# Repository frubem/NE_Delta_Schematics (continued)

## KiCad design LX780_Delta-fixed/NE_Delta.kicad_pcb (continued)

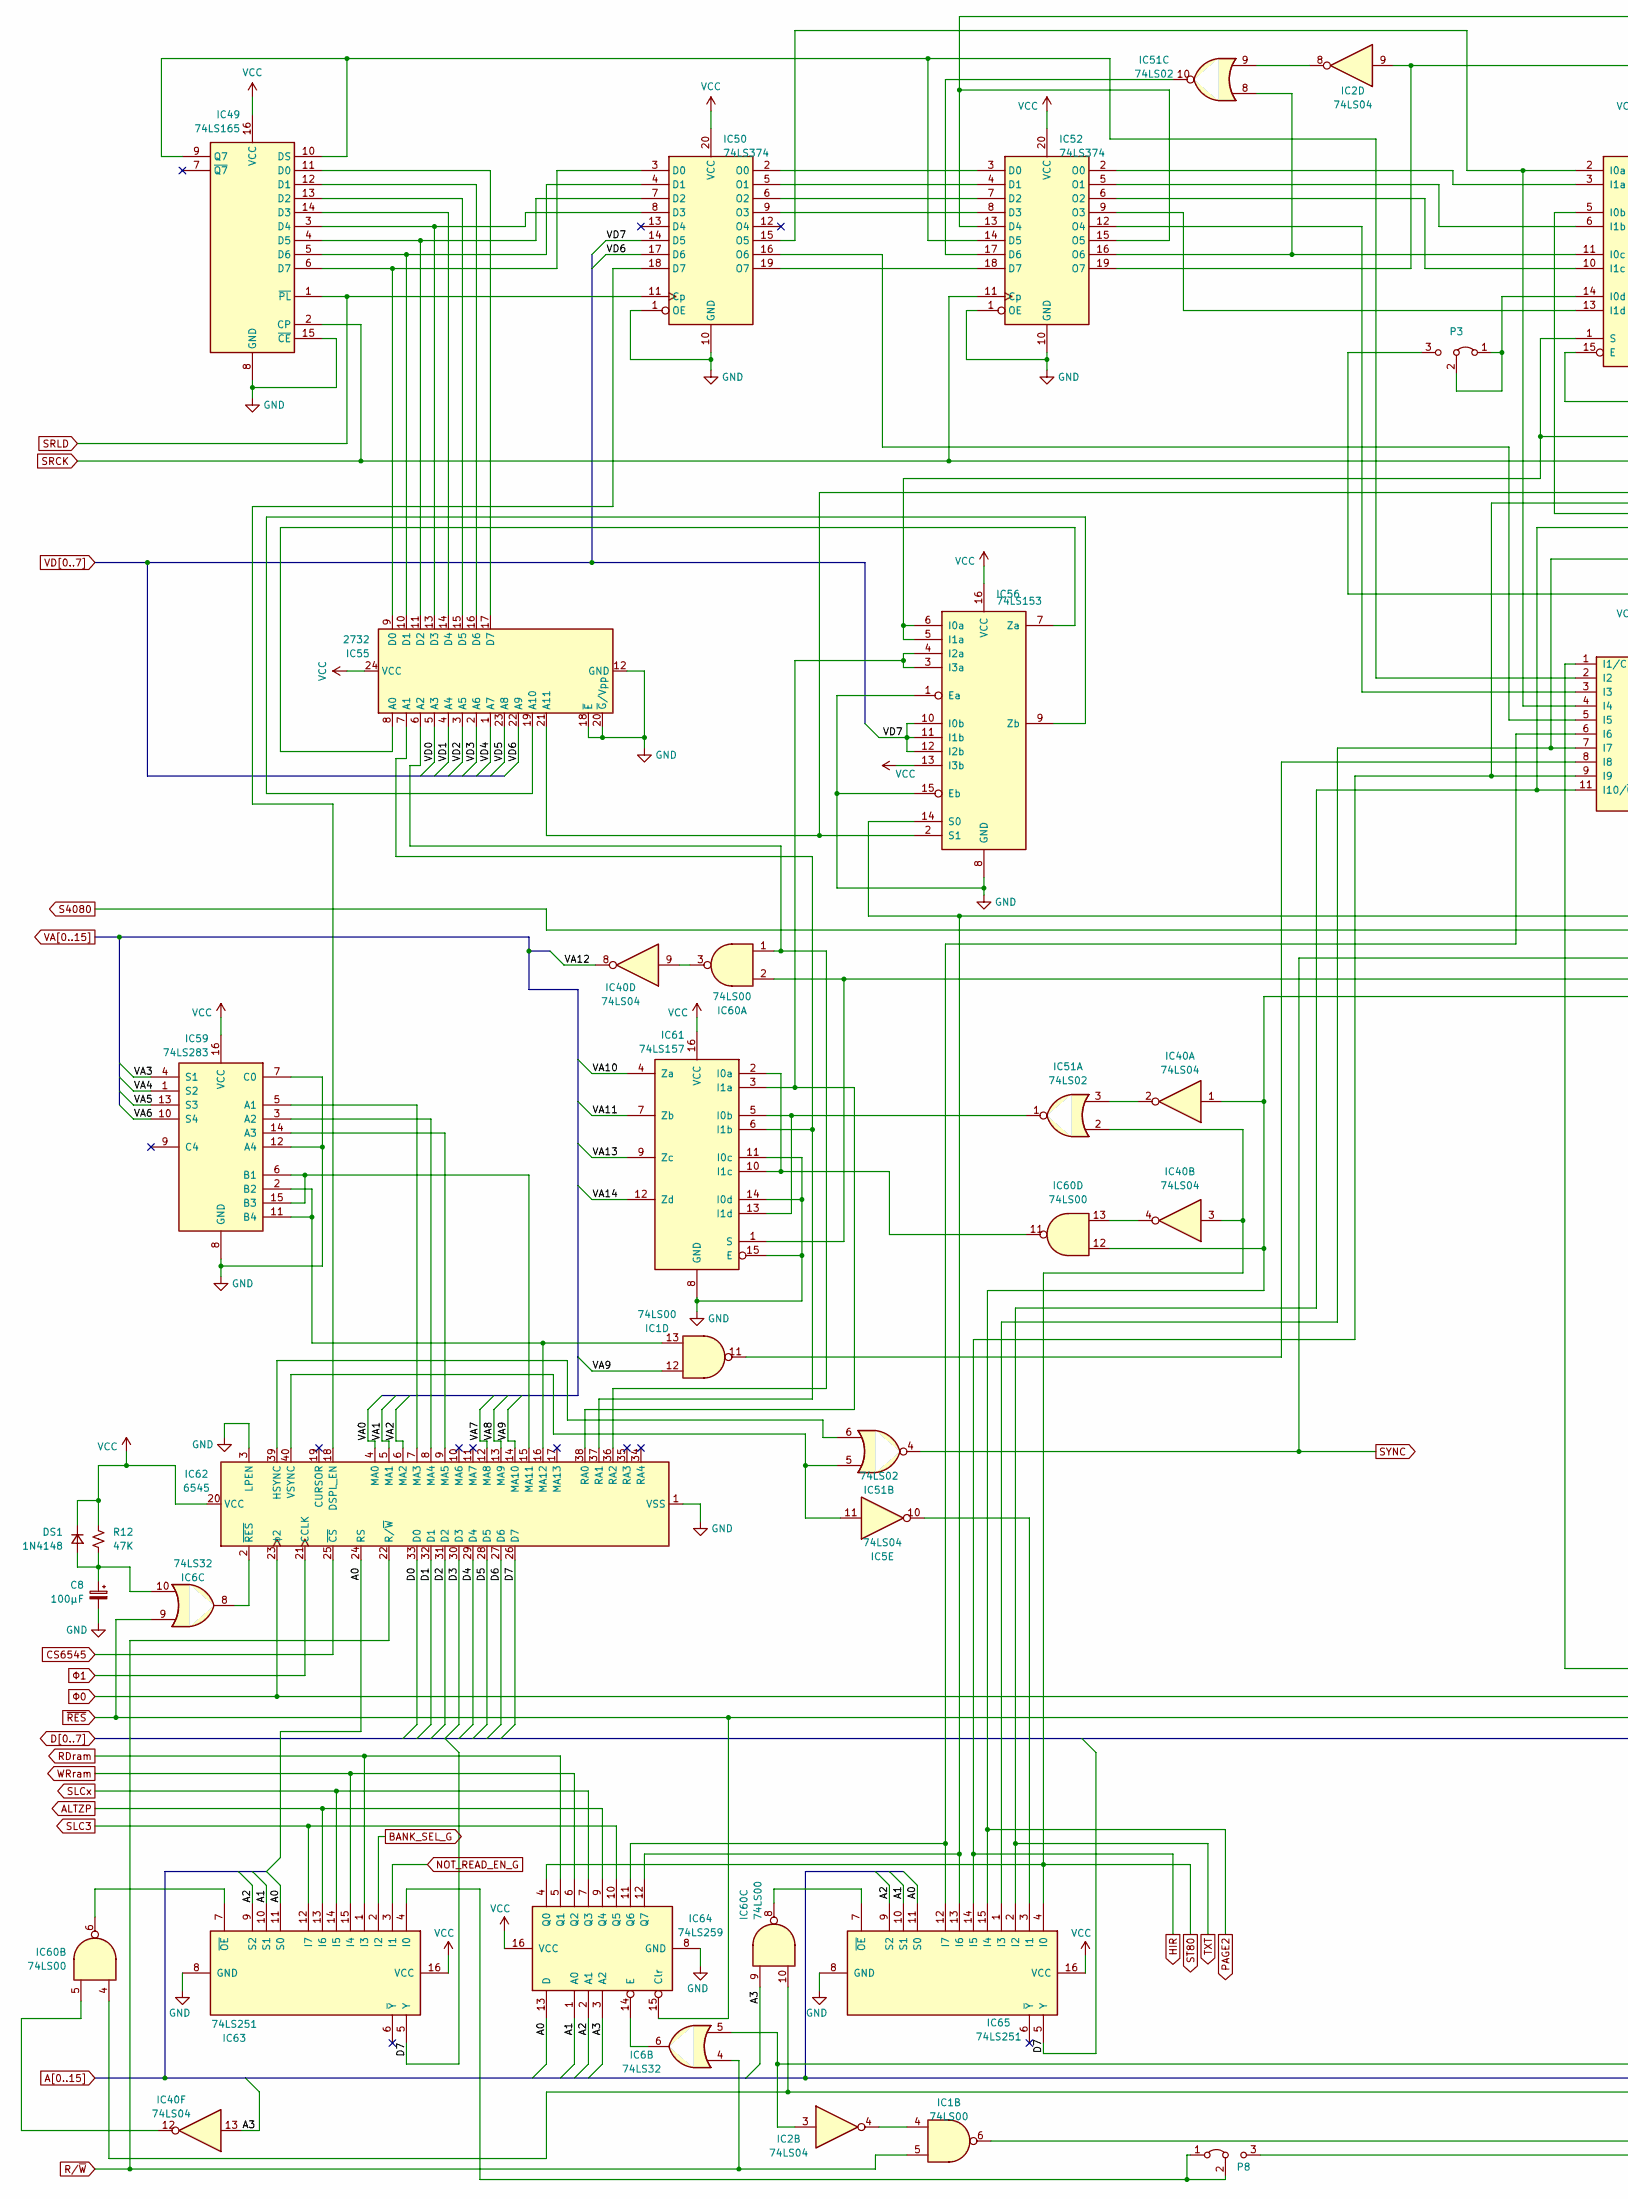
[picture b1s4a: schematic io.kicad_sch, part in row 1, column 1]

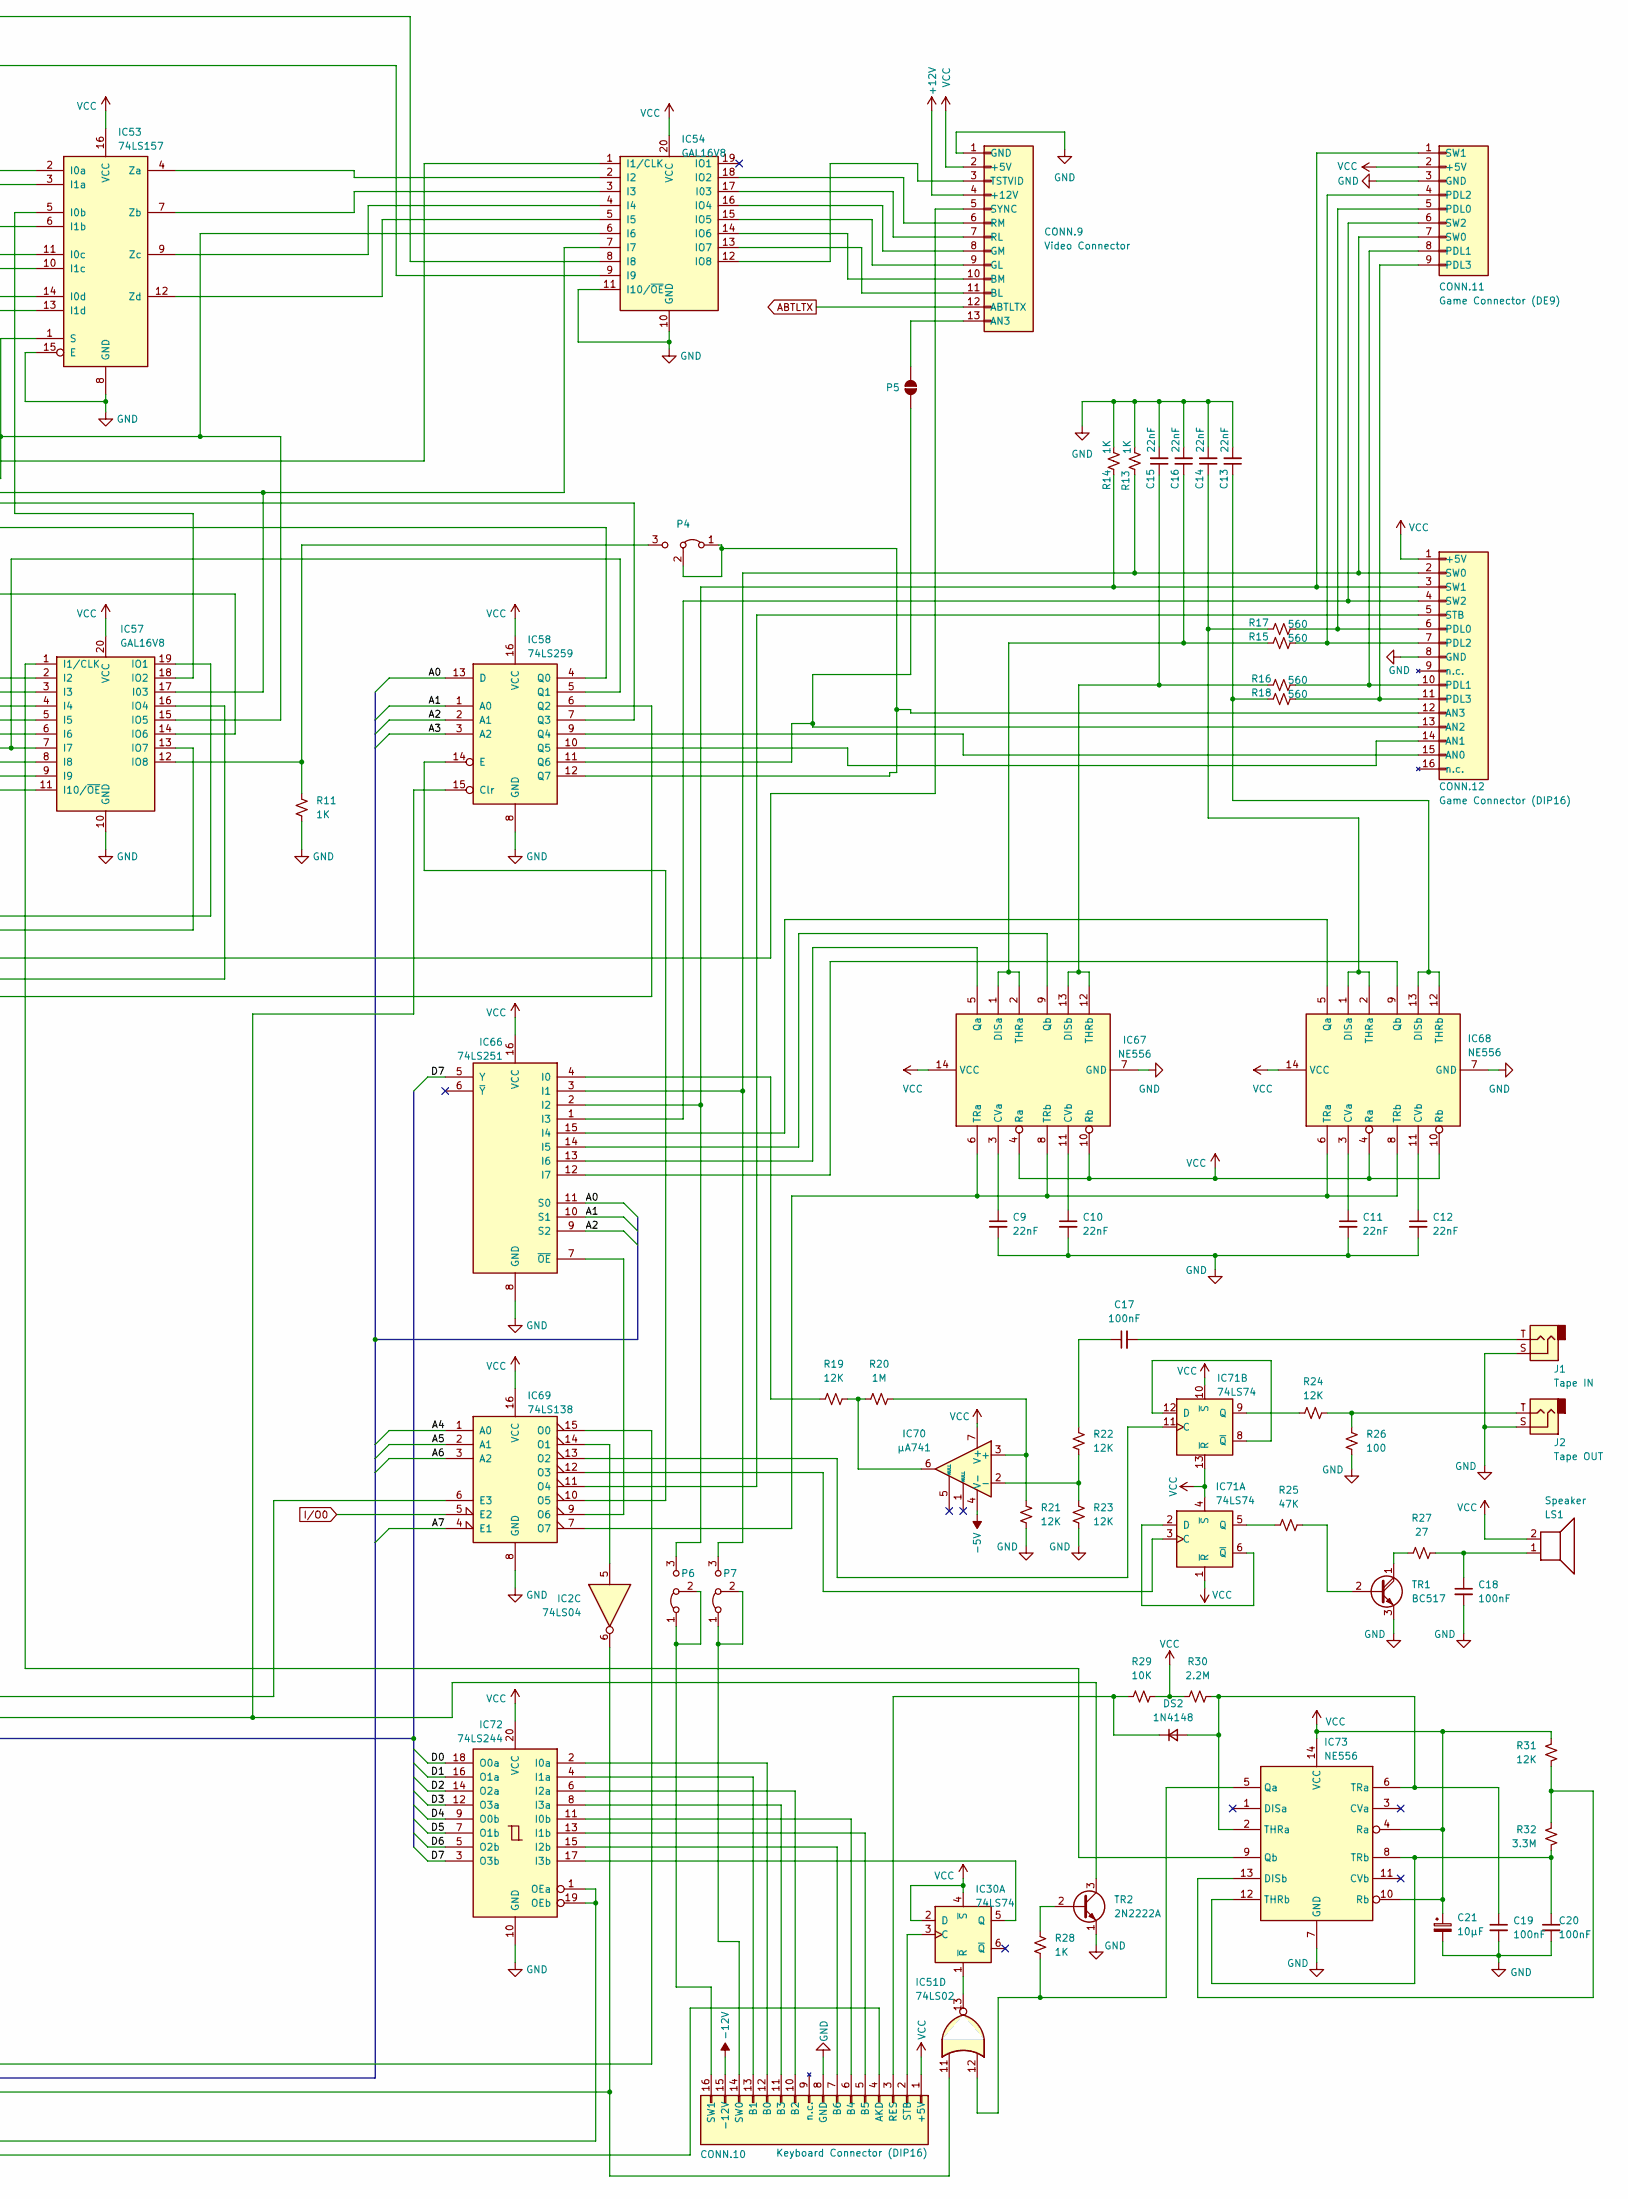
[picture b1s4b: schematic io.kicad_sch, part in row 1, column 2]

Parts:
C8: 100μF; CP_Radial_D8.0mm_P3.50mm
C9, C10, C11, C12, C13, C14, C15, C16: 22nF; C_Disc_D6.0mm_W2.5mm_P5.00mm
C17, C18, C19, C20: 100nF; C_Disc_D6.0mm_W2.5mm_P5.00mm
C21: 10μF; CP_Radial_D8.0mm_P3.50mm
CONN.9: Video Connector; PinSocket_1x13_P2.54mm_Vertical
CONN.10: Keyboard Connector (DIP16); DIP-16_W7.62mm
CONN.11: Game Connector (DE9); DSUB-9_Socket_Horizontal
CONN.12: Game Connector (DIP16); DIP-16_W7.62mm
DS1, DS2: 1N4148; D_DO-35_SOD27_P15.24mm_Horizontal
IC1, IC60: 74LS00; DIP-14_W7.62mm
IC2, IC5, IC40: 74LS04; DIP-14_W7.62mm
IC6: 74LS32; DIP-14_W7.62mm
IC30, IC71: 74LS74; DIP-14_W7.62mm
IC49: 74LS165; DIP-16_W7.62mm
IC50, IC52: 74LS374; DIP-20_W7.62mm
IC51: 74LS02; DIP-14_W7.62mm
IC53, IC61: 74LS157; DIP-16_W7.62mm
IC54, IC57: GAL16V8; DIP-20_W7.62mm
IC55: 2732; DIP-24_W15.24mm
IC56: 74LS153; DIP-16_W7.62mm
IC58, IC64: 74LS259; DIP-16_W7.62mm
IC59: 74LS283; DIP-16_W7.62mm
IC62: 6545; DIP-40_W15.24mm
IC63, IC65, IC66: 74LS251; DIP-16_W7.62mm
IC67, IC68, IC73: NE556; DIP-14_W7.62mm
IC69: 74LS138; DIP-16_W7.62mm
IC70: μA741; DIP-8_W7.62mm
IC72: 74LS244; DIP-20_W7.62mm
J1: Tape IN; Jack_3.5mm_CUI_SJ1-3513N_Horizontal
J2: Tape OUT; Jack_3.5mm_CUI_SJ1-3513N_Horizontal
LS1: Speaker; PinHeader_1x02_P2.54mm_Horizontal
P3, P4, P6, P7, P8: Jumper_3_Bridged12; PinHeader_1x03_P2.54mm_Vertical
P5: SolderJumper_2_Open; SolderJumper-2_P1.3mm_Open_RoundedPad1.0x1.5mm
R11, R13, R14, R28: 1K; R_Axial_DIN0309_L9.0mm_D3.2mm_P15.24mm_Horizontal
R12, R25: 47K; R_Axial_DIN0309_L9.0mm_D3.2mm_P15.24mm_Horizontal
R15, R16, R17, R18: 560; R_Axial_DIN0309_L9.0mm_D3.2mm_P15.24mm_Horizontal
R19, R21, R22, R23, R24, R31: 12K; R_Axial_DIN0309_L9.0mm_D3.2mm_P15.24mm_Horizontal
R20: 1M; R_Axial_DIN0309_L9.0mm_D3.2mm_P15.24mm_Horizontal
R26: 100; R_Axial_DIN0309_L9.0mm_D3.2mm_P15.24mm_Horizontal
R27: 27; R_Axial_DIN0309_L9.0mm_D3.2mm_P15.24mm_Horizontal
R29: 10K; R_Axial_DIN0309_L9.0mm_D3.2mm_P15.24mm_Horizontal
R30: 2.2M; R_Axial_DIN0309_L9.0mm_D3.2mm_P15.24mm_Horizontal
R32: 3.3M; R_Axial_DIN0309_L9.0mm_D3.2mm_P15.24mm_Horizontal
TR1: BC517; TO-92_HandSolder
TR2: 2N2222A; TO-92_HandSolder

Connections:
+5V: C21.1, CONN.9.2 (+5V), CONN.10.1 (+5V), CONN.11.2 (+5V), CONN.12.1 (+5V), DS1.1 (K), IC30.2 (D), IC30.4 (~S), IC49.16 (VCC), IC50.20 (VCC), IC52.20 (VCC), IC53.16 (VCC), IC54.20 (VCC), IC55.24 (VCC), IC56.13 (I3b), IC56.16 (VCC), IC57.20 (VCC), IC58.16 (VCC), IC59.16 (VCC), IC61.16 (VCC), IC62.20 (VCC), IC63.16 (VCC), IC64.16 (VCC), IC65.16 (VCC), IC66.16 (VCC), IC67.4 (Ra), IC67.10 (Rb), IC67.14 (VCC), IC68.4 (Ra), IC68.10 (Rb), IC68.14 (VCC), IC69.16 (VCC), IC70.7 (V+), IC71.1 (~R), IC71.4 (~S), IC71.10 (~S), IC71.13 (~R), IC72.20 (VCC), IC73.4 (Ra), IC73.10 (Rb), IC73.14 (VCC), LS1.2, R12.1, R29.2, R30.1, R31.1; also elsewhere on the board
+12V: CONN.9.4 (+12V); also elsewhere on the board
-5V: IC70.4 (V-); also elsewhere on the board
-12V: CONN.10.15 (-12V); also elsewhere on the board
A0: IC58.13 (D), IC62.24 (RS), IC63.11 (S0), IC64.13 (D), IC65.11 (S0), IC66.11 (S0); also elsewhere on the board
A1: IC58.1 (A0), IC63.10 (S1), IC64.1 (A0), IC65.10 (S1), IC66.10 (S1); also elsewhere on the board
A2: IC58.2 (A1), IC63.9 (S2), IC64.2 (A1), IC65.9 (S2), IC66.9 (S2); also elsewhere on the board
A3: IC40.13, IC58.3 (A2), IC60.9, IC64.3 (A2); also elsewhere on the board
A4: IC69.1 (A0); also elsewhere on the board
A5: IC69.2 (A1); also elsewhere on the board
A6: IC69.3 (A2); also elsewhere on the board
A7: IC69.4 (E1); also elsewhere on the board
ABTLTX: CONN.9.12 (ABTLTX); also elsewhere on the board
ALTZP: IC63.13 (I6), IC64.9 (Q4); also elsewhere on the board
CS6545: IC62.25 (~CS); also elsewhere on the board
D0: IC62.33 (D0), IC72.18 (O0a); also elsewhere on the board
D1: IC62.32 (D1), IC72.16 (O1a); also elsewhere on the board
D2: IC62.31 (D2), IC72.14 (O2a); also elsewhere on the board
D3: IC62.30 (D3), IC72.12 (O3a); also elsewhere on the board
D4: IC62.29 (D4), IC72.9 (O0b); also elsewhere on the board
D5: IC62.28 (D5), IC72.7 (O1b); also elsewhere on the board
D6: IC62.27 (D6), IC72.5 (O2b); also elsewhere on the board
D7: IC62.26 (D7), IC63.5 (Y), IC65.5 (Y), IC66.5 (Y), IC72.3 (O3b); also elsewhere on the board
GND: C8.2, C9.2, C10.2, C11.2, C12.2, C13.2, C14.2, C15.2, C16.2, C18.2, C19.2, C20.2, C21.2, CONN.9.1 (GND), CONN.10.8 (GND), CONN.11.3 (GND), CONN.12.8 (GND), IC49.8 (GND), IC49.15 (~CE), IC50.1 (OE), IC50.10 (GND), IC52.1 (OE), IC52.10 (GND), IC53.8 (GND), IC53.15 (E), IC54.10 (GND), IC54.11 (I10/~OE), IC55.12 (GND), IC55.18 (~E), IC55.20 (~G/Vpp), IC56.1 (Ea), IC56.8 (GND), IC56.15 (Eb), IC57.10 (GND), IC58.8 (GND), IC59.7 (C0), IC59.8 (GND), IC59.12 (A4), IC61.8 (GND), IC61.11 (I0c), IC61.14 (I0d), IC61.15 (E), IC62.1 (VSS), IC62.3 (LPEN), IC63.8 (GND), IC64.8 (GND), IC65.8 (GND), IC66.8 (GND), IC67.7 (GND), IC68.7 (GND), IC69.8 (GND), IC72.10 (GND), IC73.7 (GND), J1.S, J2.S, R11.2, R13.2, R14.2, R21.2, R23.2, R26.2, TR1.3 (E), TR2.1 (E); also elsewhere on the board
HIR: IC57.9 (I9), IC58.7 (Q3), IC65.14 (I5); also elsewhere on the board
I/O0: IC69.5 (E2); also elsewhere on the board
unnamed: C17.1, R22.1
unnamed: C17.2, J1.T
unnamed: C18.1, LS1.1, R27.2
unnamed: CONN.9.11 (BL), IC54.13 (IO7)
unnamed: CONN.9.10 (BM), IC54.14 (IO6)
unnamed: CONN.9.9 (GL), IC54.15 (IO5)
unnamed: CONN.9.8 (GM), IC54.16 (IO4)
unnamed: CONN.9.7 (RL), IC54.17 (I03)
unnamed: CONN.9.6 (RM), IC54.18 (IO2)
unnamed: CONN.9.3 (TSTVID), IC54.12 (IO8)
unnamed: CONN.10.4 (AKD), P8.3 (B)
unnamed: CONN.10.12 (B0), IC72.2 (I0a)
unnamed: CONN.10.13 (B1), IC72.4 (I1a)
unnamed: CONN.10.10 (B2), IC72.6 (I2a)
unnamed: CONN.10.11 (B3), IC72.8 (I3a)
unnamed: CONN.10.6 (B4), IC72.11 (I0b)
unnamed: CONN.10.5 (B5), IC72.13 (I1b)
unnamed: CONN.10.7 (B6), IC72.15 (I2b)
unnamed: CONN.10.3 (RES), DS2.1 (K), R29.1
unnamed: CONN.10.2 (STB), IC30.3 (C)
unnamed: CONN.10.14 (SW0), P7.1 (A), P7.2 (C)
unnamed: CONN.10.16 (SW1), P6.1 (A), P6.2 (C)
unnamed: CONN.11.5 (PDL0), CONN.12.6 (PDL0), R17.2
unnamed: CONN.11.8 (PDL1), CONN.12.10 (PDL1), R16.2
unnamed: CONN.11.4 (PDL2), CONN.12.7 (PDL2), R15.2
unnamed: CONN.11.9 (PDL3), CONN.12.11 (PDL3), R18.2
unnamed: CONN.11.7 (SW0), CONN.12.2 (SW0), IC66.3 (I1), P7.3 (B), R13.1
unnamed: CONN.11.1 (SW1), CONN.12.3 (SW1), IC66.2 (I2), P6.3 (B), R14.1
unnamed: CONN.11.6 (SW2), CONN.12.4 (SW2), IC66.1 (I3)
unnamed: CONN.12.15 (AN0), IC58.9 (Q4)
unnamed: CONN.12.14 (AN1), IC58.10 (Q5)
unnamed: CONN.12.12 (AN3), IC58.12 (Q7), P4.1 (A), P4.2 (C)
unnamed: CONN.12.5 (STB), IC69.11 (O4)
unnamed: C8.1, DS1.2 (A), IC6.10, R12.2
unnamed: C19.1, DS2.2 (A), IC73.2 (THRa), IC73.6 (TRa), R30.2
unnamed: IC1.4, IC2.4
unnamed: IC2.6, IC51.11, IC60.4, IC60.10
unnamed: IC2.8, IC51.9
unnamed: IC30.5 (Q), IC72.17 (I3b)
unnamed: IC30.1 (~R), IC51.13
unnamed: IC40.2, IC51.3
unnamed: IC40.4, IC60.13
unnamed: IC40.9, IC60.3
unnamed: IC40.12, IC60.5
unnamed: IC49.11 (D0), IC55.17 (D7)
unnamed: IC49.12 (D1), IC55.16 (D6)
unnamed: IC49.13 (D2), IC55.15 (D5)
unnamed: IC49.14 (D3), IC55.14 (D4)
unnamed: IC49.3 (D4), IC50.8 (D3), IC55.13 (D3)
unnamed: IC49.4 (D5), IC50.7 (D2), IC55.11 (D2)
unnamed: IC49.5 (D6), IC50.4 (D1), IC55.10 (D1)
unnamed: IC49.6 (D7), IC50.3 (D0), IC55.9 (D0)
unnamed: IC49.9 (Q7), IC49.10 (DS), IC52.14 (D5), IC57.2 (I2)
unnamed: IC50.18 (D7), IC62.18 (DSPL_EN)
unnamed: IC50.2 (O0), IC52.3 (D0)
unnamed: IC50.5 (O1), IC52.4 (D1)
unnamed: IC50.6 (O2), IC52.7 (D2)
unnamed: IC50.9 (O3), IC52.8 (D3)
unnamed: IC50.15 (O5), IC53.2 (I0a), IC57.4 (I4)
unnamed: IC50.16 (O6), IC57.5 (I5)
unnamed: IC50.19 (O7), IC52.18 (D7)
unnamed: IC52.13 (D4), IC52.15 (O5), IC54.8 (I8)
unnamed: IC51.10, IC52.17 (D6)
unnamed: IC52.2 (O0), IC53.3 (I1a)
unnamed: IC52.5 (O1), IC53.6 (I1b)
unnamed: IC52.6 (O2), IC53.10 (I1c)
unnamed: IC52.9 (O3), IC53.13 (I1d)
unnamed: IC52.12 (O4), IC57.3 (I3)
unnamed: IC51.8, IC52.16 (O6), IC53.11 (I0c)
unnamed: IC2.9, IC52.19 (O7), IC54.9 (I9)
unnamed: IC53.5 (I0b), IC57.18 (IO2)
unnamed: IC53.14 (I0d), P3.1 (A), P3.2 (C)
unnamed: IC53.1 (S), IC54.6 (I6), IC56.5 (I1a), IC56.6 (I0a), IC57.15 (IO5)
unnamed: IC53.4 (Za), IC54.2 (I2)
unnamed: IC53.7 (Zb), IC54.3 (I3)
unnamed: IC53.9 (Zc), IC54.4 (I4)
unnamed: IC53.12 (Zd), IC54.5 (I5)
unnamed: IC54.7 (I7), IC55.21 (A11), IC56.2 (S1), IC57.17 (I03)
unnamed: IC55.8 (A0), IC56.7 (Za)
unnamed: IC55.7 (A1), IC61.6 (I1b), IC62.37 (RA1)
unnamed: IC55.6 (A2), IC60.1, IC62.36 (RA2)
unnamed: IC55.19 (A10), IC56.9 (Zb)
unnamed: IC56.3 (I3a), IC56.4 (I2a), IC61.3 (I1a), IC62.38 (RA0)
unnamed: IC56.14 (S0), IC57.19 (IO1), IC64.12 (Q7), IC65.13 (I6)
unnamed: IC57.1 (I1/CLK), IC73.9 (Qb)
unnamed: IC57.6 (I6), IC64.11 (Q6), IC65.12 (I7)
unnamed: IC57.7 (I7), IC58.5 (Q1), IC65.1 (I3)
unnamed: IC1.11, IC57.8 (I8)
unnamed: IC57.16 (IO4), IC60.2, IC61.1 (S)
unnamed: IC57.14 (IO6), P3.3 (B)
unnamed: IC57.12 (IO8), P4.3 (B), R11.1
unnamed: IC58.14 (E), IC69.10 (O5)
unnamed: IC59.5 (A1), IC62.7 (MA3)
unnamed: IC59.3 (A2), IC62.8 (MA4)
unnamed: IC59.14 (A3), IC62.9 (MA5)
unnamed: IC59.6 (B1), IC59.15 (B3), IC62.15 (MA11)
unnamed: IC1.13, IC59.2 (B2), IC59.11 (B4), IC62.16 (MA12)
unnamed: IC60.11, IC61.2 (I0a), IC61.10 (I1c)
unnamed: IC51.1, IC61.5 (I0b), IC61.13 (I1d)
unnamed: IC51.6, IC62.39 (HSYNC)
unnamed: IC5.11, IC51.5, IC62.40 (VSYNC)
unnamed: IC6.8, IC62.2 (~RES)
unnamed: IC63.4 (I0), P8.1 (A), P8.2 (C)
unnamed 261: IC63.3 (I1); also elsewhere on the board
unnamed: IC60.6, IC63.7 (~OE)
unnamed: IC6.6, IC64.14 (E)
unnamed: IC5.10, IC65.3 (I1)
unnamed: IC60.8, IC65.7 (~OE)
unnamed: IC66.4 (I0), R19.1
unnamed: IC66.15 (I4), IC68.5 (Qa)
unnamed: IC66.14 (I5), IC67.9 (Qb)
unnamed: IC66.13 (I6), IC67.5 (Qa)
unnamed: IC66.12 (I7), IC68.9 (Qb)
unnamed: IC66.7 (~OE), IC69.9 (O6)
unnamed: C9.1, IC67.3 (CVa)
unnamed: C10.1, IC67.11 (CVb)
unnamed: C16.1, IC67.1 (DISa), IC67.2 (THRa), R15.1
unnamed: C15.1, IC67.12 (THRb), IC67.13 (DISb), R16.1
unnamed: IC67.6 (TRa), IC67.8 (TRb), IC68.6 (TRa), IC68.8 (TRb), IC69.7 (O7)
unnamed: C11.1, IC68.3 (CVa)
unnamed: C12.1, IC68.11 (CVb)
unnamed: C14.1, IC68.1 (DISa), IC68.2 (THRa), R17.1
unnamed: C13.1, IC68.12 (THRb), IC68.13 (DISb), R18.1
unnamed: IC2.3, IC6.5, IC69.15 (O0)
unnamed: IC2.5, IC69.14 (O1)
unnamed: IC69.13 (O2), IC71.11 (C)
unnamed: IC69.12 (O3), IC71.3 (C)
unnamed: IC70.3 (+), R20.2, R21.1
unnamed: IC70.2 (-), R22.2, R23.1
unnamed: IC70.6, R19.2, R20.1
unnamed: IC71.2 (D), IC71.6 (~Q)
unnamed: IC71.5 (Q), R25.1
unnamed: IC71.8 (~Q), IC71.12 (D)
unnamed: IC71.9 (Q), R24.1
unnamed: IC1.6, IC72.1 (OEa), IC72.19 (OEb)
unnamed: IC73.13 (DISb), R31.2, R32.1
unnamed: IC51.12, IC73.5 (Qa), R28.2
unnamed: C20.1, IC73.8 (TRb), IC73.12 (THRb), R32.2
unnamed: J2.T, R24.2, R26.1
unnamed: R25.2, TR1.2 (B)
unnamed: R27.1, TR1.1 (C)
unnamed: R28.1, TR2.2 (B)
PAGE2: IC40.1, IC58.6 (Q2), IC60.12, IC65.15 (I4); also elsewhere on the board
RDram: IC63.1 (I3), IC64.5 (Q1); also elsewhere on the board
R/~W: IC1.5, IC6.4, IC62.22 (R/~W); also elsewhere on the board
S4080: IC57.13 (IO7); also elsewhere on the board
SLC3: IC63.12 (I7), IC64.10 (Q5); also elsewhere on the board
SLCx: IC63.14 (I5), IC64.7 (Q3); also elsewhere on the board
SRCK: IC49.2 (CP), IC52.11 (Cp), IC54.1 (I1/CLK); also elsewhere on the board
SRLD: IC49.1 (~PL), IC50.11 (Cp); also elsewhere on the board
ST80: IC40.3, IC51.2, IC64.4 (Q0), IC65.4 (I0); also elsewhere on the board
SYNC: CONN.9.5 (SYNC), IC51.4; also elsewhere on the board
TXT: IC57.11 (I10/~OE), IC58.4 (Q0), IC65.2 (I2); also elsewhere on the board
VA0: IC62.4 (MA0); also elsewhere on the board
VA1: IC62.5 (MA1); also elsewhere on the board
VA2: IC62.6 (MA2); also elsewhere on the board
VA3: IC59.4 (S1); also elsewhere on the board
VA4: IC59.1 (S2); also elsewhere on the board
VA5: IC59.13 (S3); also elsewhere on the board
VA6: IC59.10 (S4); also elsewhere on the board
VA7: IC62.12 (MA8); also elsewhere on the board
VA8: IC62.13 (MA9); also elsewhere on the board
VA9: IC1.12, IC62.14 (MA10); also elsewhere on the board
VA10: IC61.4 (Za); also elsewhere on the board
VA11: IC61.7 (Zb); also elsewhere on the board
VA12: IC40.8; also elsewhere on the board
VA13: IC61.9 (Zc); also elsewhere on the board
VA14: IC61.12 (Zd); also elsewhere on the board
VD0: IC55.5 (A3); also elsewhere on the board
VD1: IC55.4 (A4); also elsewhere on the board
VD2: IC55.3 (A5); also elsewhere on the board
VD3: IC55.2 (A6); also elsewhere on the board
VD4: IC55.1 (A7); also elsewhere on the board
VD5: IC55.23 (A8); also elsewhere on the board
VD6: IC50.17 (D6), IC55.22 (A9); also elsewhere on the board
VD7: IC50.14 (D5), IC56.10 (I0b), IC56.11 (I1b), IC56.12 (I2b); also elsewhere on the board
WRram: IC63.15 (I4), IC64.6 (Q2); also elsewhere on the board
~RES: IC6.9, IC58.15 (Clr), IC64.15 (Clr), TR2.3 (C); also elsewhere on the board
Φ0: IC62.23 (ϕ2), IC69.6 (E3); also elsewhere on the board
Φ1: IC62.21 (CCLK); also elsewhere on the board

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
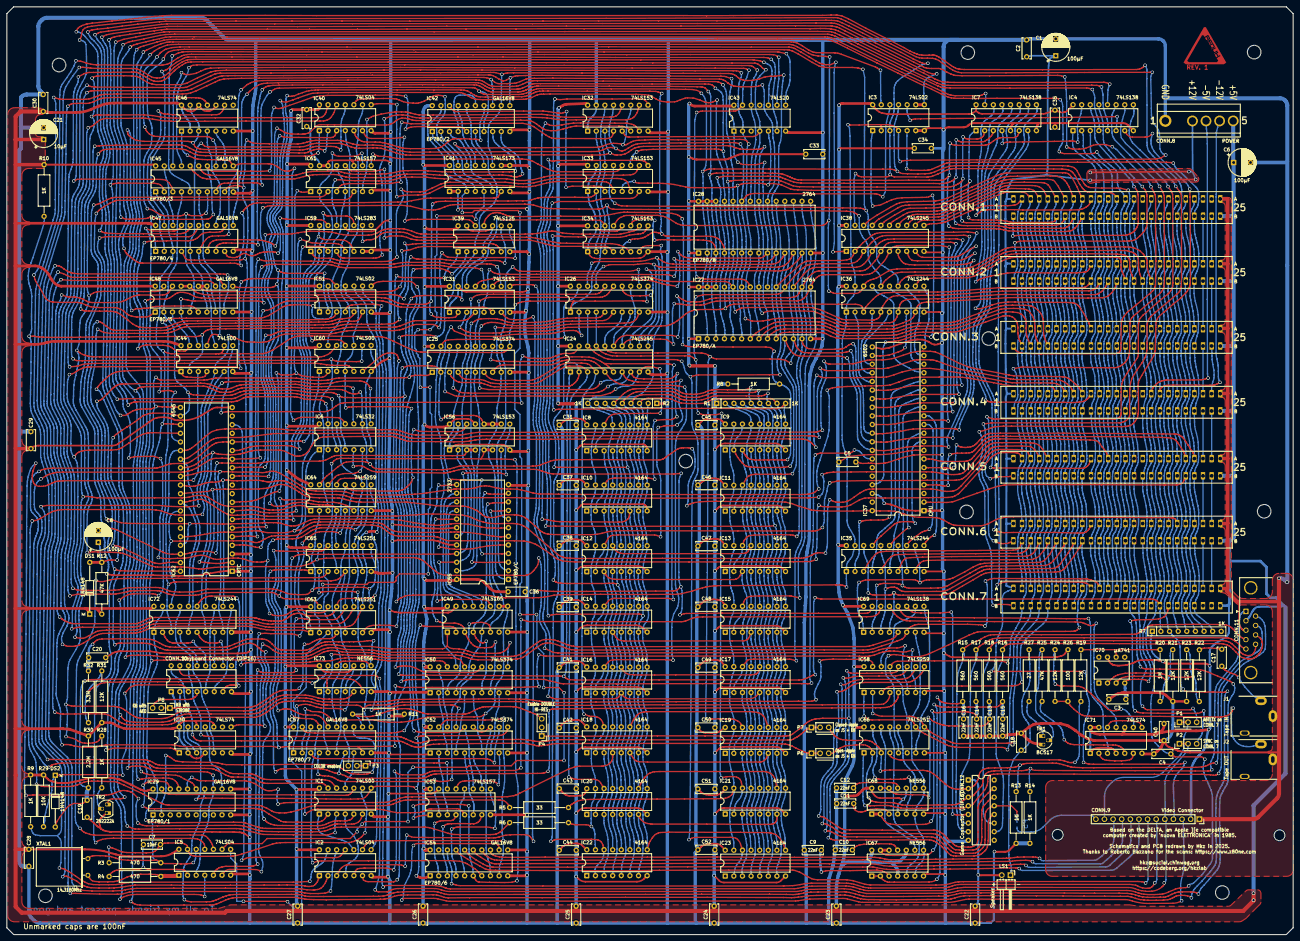
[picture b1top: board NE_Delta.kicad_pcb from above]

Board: 2 copper layers, 379.1 x 273.4 mm, 185 parts (1 on the bottom side), 350 nets.

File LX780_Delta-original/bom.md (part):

# LX780 DELTA motherboard - BOM

| Component              | Qty | Type / Value                                            | Notes                                                                |
| ---------------------- | --- | ------------------------------------------------------- | -------------------------------------------------------------------- |
| C1, C6                 |  2  | 100uF/25V+ electrolytic capacitor, 5mm pitch            |                                                                      |
| C2-C5, C17-C20, C22-C52 | 39  | 100nF/25V+ MLCC capacitor, 5mm pitch                   |                                                                      |
| C7                     |  1  | 10nF/25V+ MLCC capacitor, 5mm pitch                     | Note that the silkscreen value for this is missing in rev.0          |
| C8                     |  1  | 100uF/25V+ electrolytic capacitor, 3.5mm pitch          |                                                                      |
| C9-C16                 |  8  | 22nF/25V+ MLCC capacitor, 5mm pitch                     |                                                                      |
| C21                    |  1  | 10uF/25V+ electrolytic capacitor, 3.5mm pitch           |                                                                      |
| CONN.1 - 7             |  7  | 50P (2x25) female edge connector, 2.54mm pitch          | https://aliexpress.com/item/1005008354411366.html                    |
| CONN.8                 |  1  | 6P 3.96mm pitch header                                  | Pin 2 must be removed. E.g. https://www.mouser.it/ProductDetail/Molex/26-48-2065 |
| CONN.9                 |  1  | 13P 2.54mm pitch pinsocket, straight                    |                                                                      |
| CONN.10, CONN.12       |  2  | DIP-16 socket                                           | Used as keyboard/joystick connectors. My advice is to use turned pin sockets for these |
| CONN.11                |  1  | DSUB-9, female, horizontal                              |                                                                      |
| DS1, DS2               |  2  | 1N4148 diodes                                           |                                                                      |
| IC1, IC44, IC60        |  3  | 74LS00                                                  | IC1 can be replaced with an 'F variant, IC60 works fine with an 'HCT |
| IC2, IC40              |  2  | 74LS04                                                  | IC2 can be replaced with an 'HCT                                     |
| IC3, IC51              |  2  | 74LS02                                                  | IC51 can be replaced with an 'HCT                                    |
| IC4, IC7, IC69         |  3  | 74LS138                                                 |                                                                      |
| IC5                    |  1  | 74ALS04                                                 | Use an ALS or F or plain TTL here. LS provides an unstable clock     |
| IC6                    |  1  | 74LS32                                                  |                                                                      |
| IC8 - IC23             |  16 | 4164 DRAM                                               | Tested with HM4864P-2                                                |
| IC24, IC38             |  2  | 74LS245                                                 | Noticed improved stability and signal integrity using an 'HCT for IC24 |
| IC25, IC26, IC50, IC52 |  4  | 74LS374                                                 | 'HCT replacements work fine for all of these                         |
| IC27, IC28             |  2  | 2764 EPROM                                              | Tested with 27C64, 200ns                                             |
| IC29, IC42, IC45, IC47, IC48, IC54, IC57 |  7  | GAL16V8                               | Used ATF16V8BQL-15PU                                                 |
| IC30, IC46, IC71       |  3  | 74LS74                                                  |                                                                      |
| IC31, IC32, IC34, IC56 |  4  | 74LS153                                                 | Also tested with F family here, no issue                             |
| IC33                   |  1  | 74ALS153                                                | Use an ALS or F here. In my tests it resulted in a more stable DHR picture |
| IC35, IC36, IC72       |  3  | 74LS244                                                 | Improved signal integrity using 'HCT for IC35 and IC36               |
| IC37                   |  1  | 6502 DIP-40                                             | Currently using a 65C02                                              |
| IC39                   |  1  | 74LS125                                                 |                                                                      |
| IC41                   |  1  | 74LS173                                                 |                                                                      |
| IC43                   |  1  | 74LS20                                                  |                                                                      |
| IC49                   |  1  | 74LS165                                                 |                                                                      |
| IC53                   |  1  | 74LS157                                                 | Also tested with an 'ALS                                             |
| IC55                   |  1  | 2732                                                    | Tested with 27C32, 250ns                                             |
| IC58, IC64             |  2  | 74LS259                                                 |                                                                      |
| IC62                   |  1  | 6545 CRTC, DIP-40                                       |                                                                      |
| IC65, IC66             |  2  | 74LS251                                                 |                                                                      |
| IC67, IC68, IC73       |  3  | NE556                                                   |                                                                      |
| IC70                   |  1  | ua741                                                   | Op-Amp                                                               |
| J1, J2                 |  2  | SJ1-3513N audio jacks                                   | https://www.mouser.it/ProductDetail/490-SJ1-3513N                    |
| LS1                    |  1  | 2P 2.54mm pitch header, right angle                     |                                                                      |
| P1 - P4, P6 - P8       |  7  | 3P 2.54mm pitch header, straight                        |                                                                      |
| R1, R2, R7             |  3  | SIP 9 pin 1K resistor array, bussed                     |                                                                      |
| R3, R4                 |  2  | 470ohm resistor, 1/4W                                   |                                                                      |
| R5, R6                 |  2  | 33ohm resistor, 1/4W                                    |                                                                      |
| R8 - R11, R13, R14, R28|  7  | 1Kohm resistor, 1/4W                                    |                                                                      |
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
